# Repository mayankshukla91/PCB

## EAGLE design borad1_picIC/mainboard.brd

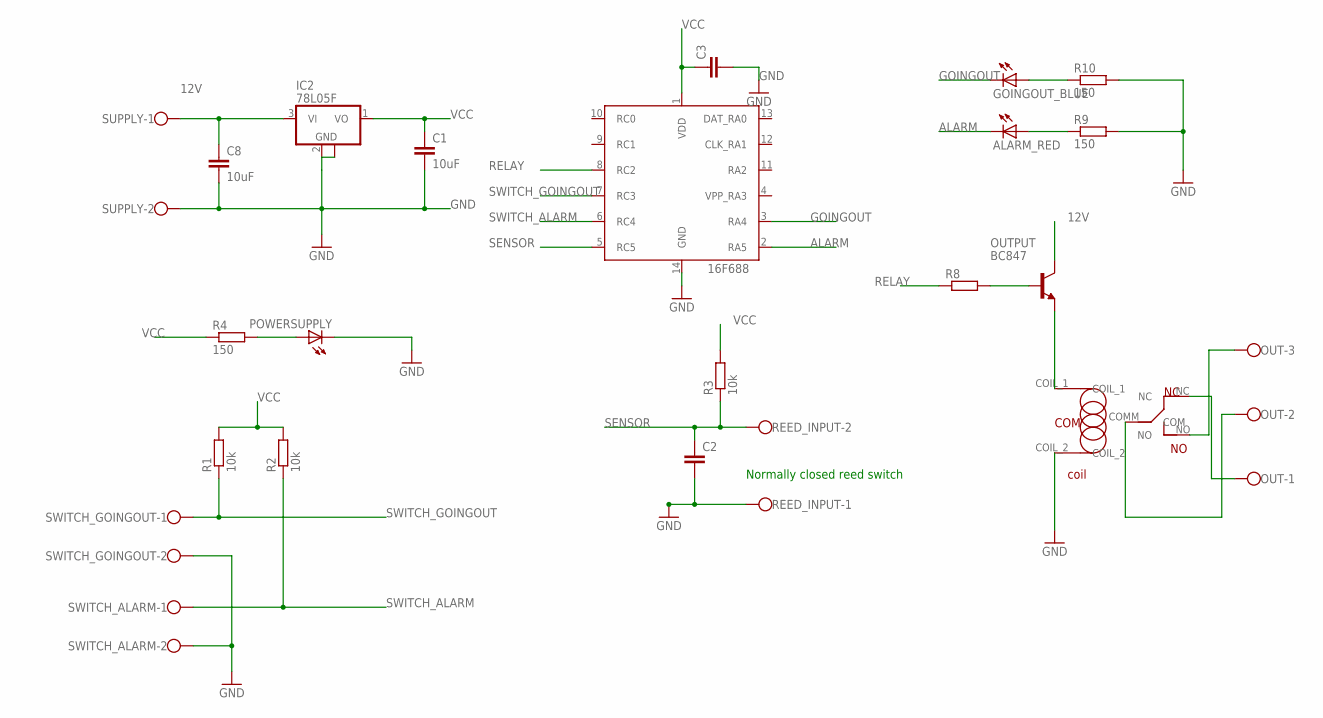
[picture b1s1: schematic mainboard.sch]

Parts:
ALARM_RED: LED5MM
C1, C8: 10uF; C0805
C2: CC0603; C0603
C3: C-EUC0805; C0805
GOINGOUT_BLUE: LED5MM
IC2: 78L05F; SOT89
OUT: W237-103
OUTPUT: BC847; SOT23
POWERSUPPLY: LED5MM
R1, R2, R3: 10k; R0603
R4, R9, R10: 150; R0603
R8: R-EU_R0603; R0603
REED_INPUT: W237-102
SUPPLY: W237-102
SWITCH_ALARM: W237-102
SWITCH_GOINGOUT: W237-102
U$1: PIC16F688SOIC14; SOIC14
U$2: JQC-3FC_RELAY; JQC-3FC

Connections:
12V: C8.1, IC2.3 (VI), OUTPUT.3 (C), SUPPLY.1
ALARM: ALARM_RED.K (C), U$1.2 (RA5)
GND: C1.2, C2.2, C3.2, C8.2, IC2.2 (GND), IC2.2@1 (GND), POWERSUPPLY.K (C), R9.2, R10.2, REED_INPUT.1, SUPPLY.2, SWITCH_ALARM.2, SWITCH_GOINGOUT.2, U$1.14 (GND), U$2.COIL_2
GOINGOUT: GOINGOUT_BLUE.K (C), U$1.3 (RA4)
unnamed: OUTPUT.2 (E), U$2.COIL_1
unnamed: GOINGOUT_BLUE.A, R10.1
unnamed: POWERSUPPLY.A, R4.2
unnamed: OUTPUT.1 (B), R8.2
unnamed: ALARM_RED.A, R9.1
unnamed: OUT.1, U$2.NC
unnamed: OUT.3, U$2.NO
unnamed: OUT.2, U$2.COMM (COM)
RELAY: R8.1, U$1.8 (RC2)
SENSOR: C2.1, R3.1, REED_INPUT.2, U$1.5 (RC5)
SWITCH_ALARM: R2.1, SWITCH_ALARM.1, U$1.6 (RC4)
SWITCH_GOINGOUT: R1.1, SWITCH_GOINGOUT.1, U$1.7 (RC3)
VCC: C1.1, C3.1, IC2.1 (VO), R1.2, R2.2, R3.2, R4.1, U$1.1 (VDD)

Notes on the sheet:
Normally closed reed switch

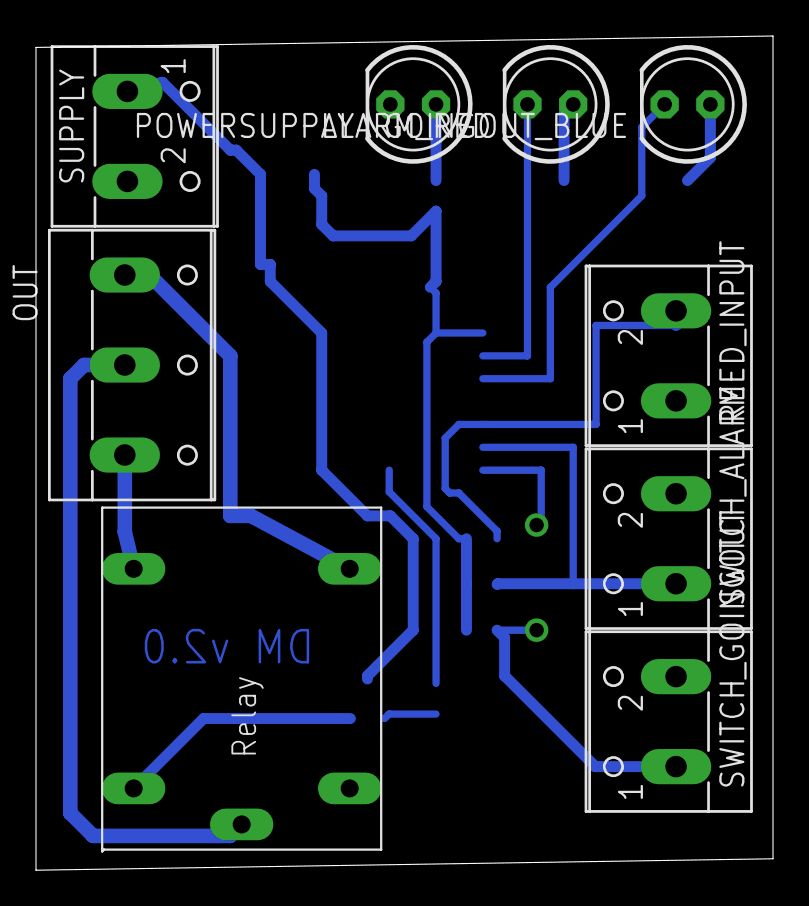
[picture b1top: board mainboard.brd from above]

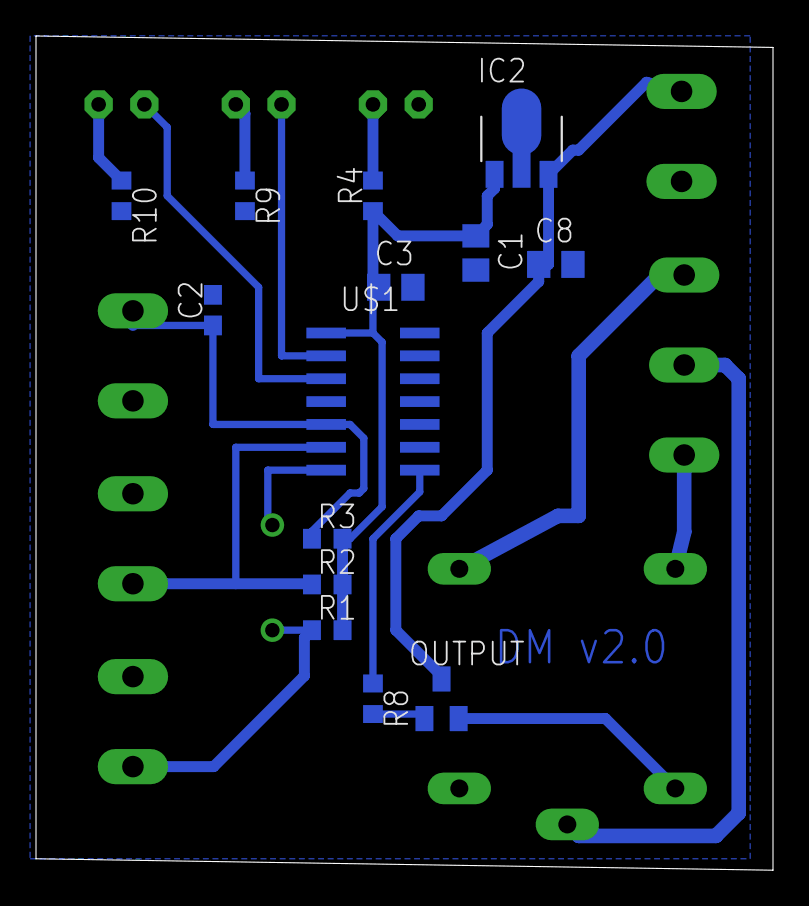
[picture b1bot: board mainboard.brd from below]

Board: 2 copper layers, 40.9 x 46.3 mm, 23 parts (14 on the bottom side), 17 nets.

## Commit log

2016-01-12 First commit...working on theft protection circuit, just basic circuit and board layout idea is ready
2016-01-19 First board ready, just figuring out the placement and connectors.
2016-01-21 Dual layer PCB routed, still needs to be checked from senior
2016-01-23 Converting everything thing to SMD, All the wires routed, components and connection modified as per suggestion from senior
2016-01-30 Changing Relay foot print to available relay and rerouted the whole PCB
